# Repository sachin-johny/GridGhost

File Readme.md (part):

<div align="center">
  
  <h2>GridGhost</h2>
  <p><strong>Macro-first PCB auto-placement engine for KiCad</strong></p>
  <p>Treats each IC + its decoupling caps as a single rigid body (a "macro"), places macros net-aware around their I/O attractors, optimizes via simulated annealing, and legalizes — all outside the KiCad editor.</p>
  <br/>
</div>

## Features

- **Macro abstraction** — an IC + its assigned decoupling caps form one `Macro` that moves rigidly through every stage of the pipeline. Caps rotate around the IC, translate with it, and stay within `MAX_CAP_IC_GAP_MM = 4.0` mm **edge-to-edge gap** of the leader — automatically, because the offset is fixed at construction time.
- **Cap classification + assignment** — caps are classified as *decoupling*, *bulk*, or *coupling* before IC assignment. Decoupling caps are distributed round-robin across ICs (one cap → exactly one IC) based on shared power rails and physical proximity.
- **Net-aware initial placement** — clusters components by net connectivity (reusing `engine/net_clustering`), then shelf-packs each cluster around the centroid of the fixed components + placed connectors it shares nets with. Per-macro gap is proportional to macro size (`max(min_gap, max_dim * 0.5)`), giving SA room to move.
- **Connector-attractor pull** — connectors are placed on the perimeter *first*, so interior placement can use their positions as attractors. Interior macros connected to a given connector get pulled toward it (`attractor_pull` blends with grid-cell fallback to prevent pile-up).
- **Simulated annealing** with four move operators:
  - **Translate** — rigid (dx, dy) on one macro
  - **Rotate** — 90/180/270 around the leader; caps orbit
  - **Swap** — exchange leader positions of two macros
  - **Displace-neighbor** — pick a macro, find a macro it overlaps, push the neighbor along the cheaper axis. Helps SA escape jammed configurations.
- **Calibrated T0** — initial temperature is set from overlap-clean sample moves only, so the HPWL gradient SA follows isn't drowned out by the β=25 overlap penalty.
- **Routability-aware cost function** — `α·HPWL + β·Overlap + γ·Boundary + γ·Keepout + rudy·RUDY + pin_density·PinDensity + cap_attraction·CapAttraction + clearance·Clearance`, with **power nets included in HPWL** (the key change vs the legacy pipeline — power-net HPWL is what gives SA gradient signal to keep caps near their assigned IC). RUDY, pin-density, cap-attraction and clearance are default-on so the placer produces a routable result out of the box. See [Cost Function](#cost-function) below.
- **Non-rectangular board outlines** — polygon outlines (connector notches, mouse-bites, castellated edges) and interior holes/keepout zones are honored end-to-end: initial placement, SA's boundary gradient, and the legalizer all clamp to the true outline instead of its outer AABB. Plain rectangular boards trace the exact pre-polygon code paths (zero behavior change).
- **Internal keepout zones** — rectangular no-place zones (mounting holes, board-edge fab notes, etc.) are penalized in the cost function and actively evicted by the legalizer's multi-pass keepout clamp, which pushes an offending macro out along its shallowest exit axis.
- **End-mating connector orientation** — barrel jacks, USB, RJ45, HDMI, D-Sub and other end-mating connectors are oriented so the mating face points outward. Face-mating connectors (terminal blocks, pin headers, SMA) use the perpendicular-to-pad-column heuristic.
- **Iterative legalizer** — grid snap → push-apart → boundary clamp, iterated up to 5 rounds to settle the push-apart ↔ clamp cycle. Cap-IC distance violations are reported as a separate stat. A post-pass **hard-DRC min-gap check** then pushes sub-0.15 mm passive-pair gaps up to the DRC minimum — TestPoint and mechanical-feature pairs are exempt (their tight placement is intentional), and any push that would create a new overlap is rolled back. Alternate strategies (`abacus`, `sa_polish`) are selectable via `--legalizer`.
- **Pad rotation propagation** — footprint rotation rewrites only the footprint's own `(at ...)` expression; per-pad `(at X Y r)` overrides are left untouched, avoiding the double-rotation that previously corrupted asymmetric footprints (SOIC/QFN/offset-pin-1 parts).
- **Edge-connector awareness** — horizontal/surface-mount connectors are placed on the board perimeter and excluded from out-of-bounds counts; vertical/THT connectors are treated as interior components.
- **Net exclusion for SA speed** — `--exclude-nets` drops near-constant-HPWL global nets (board-wide GND/VCC) from SA's per-move cost evaluation, cutting evaluation cost without changing what's optimized.
- **Debug visualization** — `--debug-bbox` draws component bounding boxes and board outline on the `Dwgs.User` layer for visual inspection in KiCad.

## Pipeline (macro-first, `place_v2`)

```text
KiCad .kicad_pcb
       │
  ┌──────────┐   parse S-expressions → BoardModel
  │  parse   │   (components, pads, nets, board outline)
  └────┬─────┘
       │
  ┌──────────┐   1. classify caps (decoupling / bulk / coupling)
  │  build   │   2. assign decoupling caps to ICs (round-robin)
  │ macros   │   3. build Macro per IC leader (+ caps as followers)
  └────┬─────┘   4. connector macros are empty (leader-only)
       │
  ┌──────────┐   place connectors on perimeter FIRST so their
  │connector │   positions can act as attractors for interior
  │ perimeter│   placement
  └────┬─────┘
       │
  ┌──────────┐   cluster interior components by net connectivity,
  │ initial │   shelf-pack each cluster around its attractor point,
  │ interior│   per-macro gap proportional to size
  └────┬─────┘
       │
  ┌──────────┐   simulated annealing on interior macros only
  │   SA     │   (translate / rotate / swap / displace-neighbor)
  │          │   T0 calibrated from overlap-clean sample moves
  └────┬─────┘
       │
  ┌──────────┐   grid snap → push-apart → boundary clamp, iterated
  │ legalize │   + hard-DRC min-gap pass (0.15 mm); reports residual
  │          │   overlaps, boundary failures, and cap-IC violations
  └────┬─────┘
       │
  Updated .kicad_pcb  (+  positions JSON)
```

## CLI Usage

```bash
# Auto-place a board (macro-first pipeline is the default)
python gridghost.py place <input.kicad_pcb> [options]

# Extract board data to JSON (no placement)
python gridghost.py extract <input.kicad_pcb> [-o output.json]

# List available board profiles
python gridghost.py profiles
```

### Place options

| Flag | Default | Description |
|------|---------|-------------|
| `-m`, `--margin` | `5.0` | Board edge margin in mm (`config.json` `placement.margin`) |
| `--grid-mm` | `0.5` | Legalization grid pitch in mm (`config.json` `legalization.grid_mm`) |
| `--sa-iterations` | `max(1500, 25×N)` | SA iterations; scales with macro count when unset (min 1500) |
| `--sa-reheat` | `3` | Number of SA reheat rounds (`config.json` `annealer.reheat_count`) |
| `--alpha` | `1.0` | HPWL weight |
| `--beta` | `25.0` | Overlap penalty weight |
| `--gamma` | `8.0` | Boundary penalty weight (also the default keepout-overlap weight) |
| `--delta` | `0.0` | Constraint-rule penalty weight (decoupling proximity, crystal-MCU, thermal grouping/separation, etc., via `engine/constraint_evaluator.py`). Opt-in — `0` preserves current behavior. |
| `--rudy-weight` | `1.0` | RUDY wire-density congestion penalty (0 = off) |
| `--pin-density-weight` | `0.2` | Pin-escape congestion penalty; complements RUDY (0 = off) |
| `--cap-attraction-weight` | `1.0` | Deadband-linear drift penalty (`max(0, dist − 5mm)`) holding rail-adjacent freed caps near their assigned IC (0 = off) |
| `--clearance-weight` | `5.0` | Pairwise routing-halo clearance charge (`max(0, 1mm − edge_gap)`) between macros; density-tapered (0 = off) |
| `--exclude-nets` | *(none)* | Net names to drop from HPWL during SA (e.g. `--exclude-nets GND +3V3`) — speeds up SA on boards with near-constant, board-wide power nets |
| `--legalizer` | `heuristic` | Overlap-resolution strategy: `heuristic` (grid snap/push-apart/clamp), `abacus` (row-based DP, kept for comparison only), or `sa_polish` (overlap-weighted SA pass) |
| `--seed` | `42` | SA RNG seed (deterministic runs) |
| `--connector-mating-margin` | `5.0` | Edge offset for perimeter connectors |
| `--macro-v2` / `--no-macro-v2` | on | Toggle macro-first pipeline. Default on. `--no-macro-v2` falls back to the legacy grid pipeline (`engine/smart_placement.py`), retained for A/B comparison. |
| `--dry-run` | off | Don't write PCB output file |
| `--debug-bbox` | off | Draw bounding boxes on Dwgs.User layer |
| `-v`, `--verbose` | off | Print per-stage cost breakdown, including routability-term initial/final values even when a term's weight is 0 |

### Examples

```bash
# Auto-place with defaults
python gridghost.py place board.kicad_pcb

# Bigger SA budget for dense boards
python gridghost.py place board.kicad_pcb --sa-iterations 3000 --sa-reheat 4

# Tighter legalization grid
python gridghost.py place board.kicad_pcb --grid-mm 0.5

# Dry run with verbose cost breakdown + debug bboxes
python gridghost.py place board.kicad_pcb -v --dry-run --debug-bbox

# Extract board data without placing
python gridghost.py extract board.kicad_pcb -o board_model.json
```

## Cost Function

```text
Total Cost = α·HPWL + β·Overlap + γ·Boundary + γ·Keepout
             + rudy·RUDY + pin_density·PinDensity
             + cap_attraction·CapAttraction + clearance·Clearance
```

- **HPWL** — Half-perimeter wirelength over all nets. **Power and ground nets are included** — this is the key change vs the legacy pipeline. Caps share power rails with their ICs, so power-net HPWL is the gradient signal that keeps caps near their assigned ICs during SA. `--exclude-nets` can drop specific board-wide nets (e.g. global GND) from this term to speed up SA without changing what it optimizes.
- **Overlap** — Sum of pairwise macro bbox intersection areas. Macros are treated as rigid rectangles (leader + follower union bbox).
- **Boundary** — Distance penalty for components whose bbox extends outside the board outline, computed via the outline's `bbox_overflow()` so it's identical on rectangles and gradient-correct on polygon/notched boards. Edge connectors (intentional overhang) are excluded.
- **Keepout** — Total area of component bboxes intersecting internal keepout zones (mounting holes, fab no-place areas). Weight defaults to `γ` (the boundary weight). Even with this term's SA gradient off, the legalizer's `_keepout_clamp` still actively evicts macros parked inside a keepout, pushing them out along the shallowest exit axis.
- **RUDY** — Wire-density congestion: each net's bounding-box "traffic" spread uniformly across the grid cells it spans, scaled by local component density (0.3× sparse boards, 1.2× dense boards, 1.0× otherwise) so amplification doesn't overshoot already-congested regions. Catches routing choke points HPWL alone is blind to. Default weight `1.0`.
- **Pin density** — Signal-pin count per grid cell (power pins excluded, target adapts to board density). Catches pin-escape congestion — dense clusters of small passives crowding a QFN's pins — that RUDY's wire-density model misses. Default weight `0.2`.
- **Cap attraction** — Deadband-linear drift penalty, `max(0, center_dist − 5mm)`, on *rail-adjacent* freed caps toward their assigned IC. Root-cause fix for shared-rail cap drift: on a rail spanning several ICs the rail's net bbox is already board-wide, so HPWL alone gives a freed cap zero gradient to stay near its IC. Default weight `1.0`.
- **Clearance** — Pairwise routing-halo charge between macro pairs: `max(0, target − edge_gap)`, where the pair's target is the **min of the two members'** per-type targets (default 1.0 mm). Pairs are exempt when both leaders are mechanical features (mounting holes, fiducials, test coupons) or when either member is a TestPoint — probe pads are intentionally pinned to IC pins, and the uniform target charged them for exactly the tight placement the design wants. HPWL's pull and the overlap term's cliff-at-touching otherwise let SA park components at a 0.00 mm gap with no room for a trace; intersecting pairs charge exactly the target so `β` stays the sole "depth" charger. Auto-tapered by interior density (1.0× ≤ 0.45 density, 0.25× ≥ 0.65). Default weight `5.0`.

All four routability terms (Keepout, RUDY, pin density, clearance) plus cap attraction are **default-on**. Pass the matching `--*-weight 0` flag to disable any of them; `-v` always reports each term's initial and final value, even at weight 0.

## Macro Model

A `Macro` is the atomic unit of placement. Construction:

1. **Leader**: a component (typically an IC) that's free to move.
2. **Followers**: caps assigned to that IC. Each follower has a *fixed offset* in leader-local coordinates, chosen at construction time by `find_cap_offset` — an 8-direction fan search at increasing edge-to-edge spacings (0.5–4.0 mm) that:
   - Rejects slots where the cap overlaps the leader or any already-placed sibling.
   - Bounds the cap's **edge-to-edge gap** to the leader by `MAX_CAP_IC_GAP_MM = 4.0` mm (the spacing itself). The gap — not the center-to-center distance — is what governs decoupling effectiveness; center-distance is size-dependent and broke every cap on ICs larger than ~9 mm.
   - Uses `max(cap_w, cap_h)/2` as the cap's half-extent on **both** axes, so the chosen gap survives leader rotation: offsets rotate with the leader but caps don't rotate with it, and a cap-height-based offset would land a non-square cap inside the leader after a 90°/270° rotation.
   - Falls back to the first leader-clear slot (smallest gap) if no slot is sibling-free.

Because offsets are fixed, the cap-IC gap can **never grow at runtime** — translating or rotating the leader applies the same rigid transform to followers. The gap is enforced by construction.

Move operators and the legalizer all operate on macros as opaque rigid bodies. Caps never get separated from their IC.

## Cap Assignment

`assign/assign_caps.py` classifies each capacitor and assigns decoupling caps to ICs. There are four classes:

- **Decoupling (rigid)** (≤ `DECAP_MAX_VALUE_F = 10e-6` F, i.e. ≤ 10 µF) — real decoupling caps whose pins on the IC land in one tight physical cluster (max pairwise pad distance on that net ≤ `RAIL_PAD_SPREAD_THRESHOLD_MM = 3.0` mm). **All** caps the netlist puts on that (IC, rail) pair become rigid `Macro` followers — the count comes from the schematic, not a manual cap — and stay within `MAX_CAP_IC_GAP_MM` edge-to-edge of the leader.
- **Decoupling (rail-adjacent)** — real decoupling caps on a rail whose pins are physically scattered across the IC footprint (e.g. a BGA power net landing on opposite corners). There's no single point to glue a tight rigid ring to, so these become standalone macros; SA holds them near their assigned IC via the **cap→IC attraction** cost term instead of rigid geometry. One IC can have, say, 6 rigid followers on one rail and 2 rail-adjacent on another — the split is per (IC, rail) pair, not a per-IC ceiling.
- **Bulk** (> 10 µF, or on a power rail no IC shares) — stays standalone, not assigned to any IC. Unparseable values default to bulk (conservative).
- **Coupling / signal** — only on signal nets (crystal loads, shields, USB D+/D-, reset filters), no power rail. Standalone.

Decoupling caps are distributed round-robin across the ICs sharing a rail. Power-rail detection also matches hierarchical labels (e.g. `/Buck/VIN`) and KiCad auto-generated net names (e.g. `Net-(U1-VIN)`) via trailing-token power-pin conventions, not just literal `+3V3`/`GND`-style names — deliberately conservative (EN/FB/COMP/SW/BOOT/VG and FET-source pins stay excluded).

A cap assigned to an IC is **only** in that IC's macro — never as a standalone macro. This is critical: if a cap were in two macros, push-apart could move the standalone cap away from its IC. One `assign_caps` classification drives rigid gluing, cap attraction, *and* the legacy `--delta` decoupling-proximity constraint — there's a single source of truth for which caps belong to which IC.

## Project Structure

```text
GridGhost/
├── gridghost.py                   # CLI entry point
├── config.py                      # Typed config loader (dataclasses)
├── config.json                    # Default config (margin, SA, legalization params)
│
├── models/
│   ├── board_model.py             # BoardModel, Component, Net, Pad, BoardOutline
│   │                              # (rectangle or polygon-with-holes; contains/
│   │                              # contains_bbox/fit_bbox_inside/bbox_overflow),
│   │                              # BoardModel.keepouts (rectangular no-place zones)
│   └── macro.py                   # Macro: leader + rigid followers
│                                  # find_cap_offset; MAX_CAP_IC_GAP_MM = 4.0 (edge-to-edge)
│
├── parsers/
│   ├── kicad_parser.py            # S-expression .kicad_pcb parser
│   └── placement_writer.py        # Write placements back to .kicad_pcb / JSON
│
├── assign/
│   └── assign_caps.py             # Classify caps (decoupling / bulk / coupling)
│                                  # and assign decoupling caps to ICs
│
├── cost/
│   ├── cost.py                    # Macro-v2 cost: α·HPWL (incl. power rails) + β·overlap
│   │                              # + γ·boundary + γ·keepout + rudy + pin_density
│   │                              # + cap_attraction + clearance
│   ├── chains.py                  # Signal-flow chain grouping for cost/SA
│   └── incremental.py             # Incremental cost delta for macro SA (all cost terms)
│
├── place/
│   ├── pipeline.py                # 5-stage orchestrator (build → connector →
│   │                              # initial → SA → legalize)
│   ├── initial.py                 # Net-aware clustered shelf-pack with
│   │                              # connector-attractor pull
│   ├── connectors.py              # Perimeter placement with pad-based rotation
│   ├── cluster.py                 # Net clustering + shelf-pack helpers for initial
│   ├── sa.py                      # Macro-aware SA (translate / rotate / swap /
│   │                              # displace-neighbor); calibrated T0
│   ├── sa_polish.py               # Overlap-weighted SA legalizer strategy (--legalizer sa_polish)
│   ├── legalizer.py               # Grid snap → push-apart → boundary clamp,
│   │                              # iterated up to 5 rounds + hard-DRC min-gap
│   │                              # pass (0.15 mm, overlap-rollback safe)
│   └── abacus_bridge.py           # Adapter from rigid Macros to the row-based
│                                  # Abacus legalizer (--legalizer abacus)
│
├── engine/                        # Shared + legacy modules.
│   ├── net_clustering.py          # Hypergraph clustering — reused by place/cluster.py
│   ├── cost_state.py              # Incremental cost state — reused by cost/, place/
│   ├── congestion.py              # Density-adaptive RUDY wire-density + pin-density
│   │                              # congestion maps — reused by cost/, place/sa
│   ├── constraint_evaluator.py    # Constraint penalty evaluation — reused by cost_state
│   ├── group_moves.py             # Macro/group move primitives — reused widely
│   ├── subcircuit_patterns.py     # Subcircuit pattern detection — reused by clustering
│   ├── _pure_graph.py             # Louvain graph core — reused by net_clustering
│   ├── cost_function.py           # Legacy cost function (used by --no-macro-v2 path)
│   ├── moves.py                   # Legacy SA move operators (--no-macro-v2)
│   ├── annealer.py                # Legacy SA engine (--no-macro-v2)
│   ├── placement_prepass.py       # Legacy decap pre-place (--no-macro-v2)
│   ├── grid_placement.py          # Legacy grid / force-directed placement (--no-macro-v2)
│   ├── quadratic_placement.py     # Legacy quadratic placer (--no-macro-v2)
│   └── smart_placement.py         # Legacy grid pipeline (--no-macro-v2)
│
├── legalization/
│   ├── legalizer.py               # Component-level legalizer (grid snap / push-apart /
│   │                              # boundary clamp), used by both pipelines
│   ├── abacus_legalizer.py        # Row-based Abacus DP legalizer
│   ├── post_legalize.py           # Post-legalization HPWL recovery (cell slide / pair swap)
│   └── spatial_grid.py            # Spatial hash grid for overlap acceleration
│
├── profiles/
│   └── board_profiles.py          # Cost weights + constraint rules per board type
│
├── utils/
│   ├── courtyard.py               # Courtyard/bbox helpers for the parser
│   ├── density.py                 # Pack-density target + board-area checks
│   └── display.py                 # CLI formatting (summary, cost, component table)
│
├── samples/
│   └── sample_board.py            # 18-component MCU peripheral sample board
│
├── tests/
│   ├── test_macro.py              # Macro model: rigid moves, bounds, cap gap, bbox
│   ├── test_assign_caps.py        # Cap classification + IC assignment (rigid/rail-adjacent split)
│   ├── test_cost.py               # HPWL / overlap / boundary / keepout / cap-attraction / clearance cost
│   ├── test_incremental_cost.py   # Incremental cost delta (all terms)
│   ├── test_chains.py             # Signal-flow chain grouping
│   ├── test_connector_placement.py# Perimeter connector placement + rotation
│   ├── test_placement_spread.py   # Placement spread / coverage
│   ├── test_abacus_bridge.py      # Macro → Abacus legalizer adapter
│   ├── test_sa_polish.py          # SA-polish legalizer strategy
│   ├── test_nonrect_outline.py    # Polygon outline geometry, parser tracing, legalizer clamps
│   ├── test_keepout.py            # Internal keepout cost + legalizer eviction
│   ├── test_pad_rotation.py       # Footprint-only rotation (no double-rotation on pads)
│   ├── test_overlap_regression.py # (currently disabled — 0 collected)
│   ├── test_phase1.py             # 87 tests: legacy pipeline + data model
│   ├── run_all.py / dashboard.py / visualizer.py   # Batch run + result dashboard harness
│   ├── run_benchmark.py           # Benchmark harness for placement quality/timing
│   ├── README.md                  # Test harness usage (run_all, dashboard, visualizer)
│   ├── test_pcbs/                 # Bundled .kicad_pcb boards + reference JSONs
│   └── external_boards/rl_pcb/    # Third-party reference boards (see its own README/LICENSE)
│
├── patches/                       # (untracked) benchmark scripts + result JSONs
│
├── logo.png
├── CLAUDE.md                      # AI assistant context
└── README.md                      # This file
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
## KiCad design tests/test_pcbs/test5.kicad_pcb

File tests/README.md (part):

# Tests & Benchmarking

Test suites, measurement harnesses, benchmark boards, and a unified
orchestrator that runs everything and produces an HTML dashboard with
per-board visualizations.

## Quick start — the unified harness

The fastest way to run everything is the **unified orchestrator**:

```bash
python tests/run_all.py                       # run all phases
python tests/run_all.py --skip-external       # skip the slow external-boards phase
python tests/run_all.py --only cbb test4      # only specific boards
python tests/run_all.py --rudy-weight 0.3     # enable RUDY in SA
python tests/run_all.py --skip-unit-tests --skip-overlap-regression  # just placement + viz
```

It runs five phases in order, collects all results, and writes a
self-contained HTML dashboard to `tests/output/<run_id>/`:

1. **Unit tests** — `python -m pytest tests/` (falls back to standalone
   `main()` if pytest is missing). Fast correctness gate (~80s).
2. **Placement pipeline** — runs `place_v2` in-process on every board
   in `tests/test_pcbs/`. Captures HPWL, overlaps, density, RUDY,
   cap-IC distances, component-type breakdown, and per-phase timing.
3. **CLI smoke test** — runs `python gridghost.py place` end-to-end on
   each board via subprocess. Catches CLI-only bugs the in-process
   path misses.
4. **Overlap regression** — runs `tests/test_overlap_regression.py`
   (self-report vs independent scan). The standing check from the
   evaluation fix.
5. **External boards** — same as Phase 2 but on
   `tests/external_boards/rl_pcb/*.kicad_pcb` (9 real-world boards).
   Adds ~10 min but catches real-world edge cases.

**Outputs** (under `tests/output/<run_id>/`):
- `dashboard.html` — the main deliverable. Open in any browser.
- `results.json` — raw metrics (for programmatic comparison).
- `<board>.svg` — per-board SVG (also inlined in the dashboard).
- `<board>_placed.kicad_pcb` — placed output (open in KiCad).
- `unit_tests.log`, `cli_smoke_<board>.log` — raw phase logs.

### Dashboard contents

The dashboard is a single self-contained HTML file (no external CSS/JS)
with:

- **Header** — run ID, timestamp, git commit, summary cards (boards,
  passing, total overlaps, total wall-time).
- **Phase summaries** — one card per phase with pass/fail status,
  passed/failed counts, duration.
- **KPI table** — one row per board, columns for components, ICs, caps,
  overlaps, Edge.Cuts present, density, HPWL, RUDY peak, SA time,
  legalize time, total time.
- **Aggregate charts** — overlaps per board (bar), timing breakdown
  (stacked bar), component-type distribution (stacked bar), cap → IC
  distance histogram.
- **Per-board detail** — inline SVG visualization + metric chips +
  overlap-pair list (collapsible) + cap-IC distance stats.

### Visualization features

The SVG visualization (rendered by `tests/visualizer.py`) shows:

- Board outline (Edge.Cuts) as a solid black rectangle.
- Margin ring (light grey fill between outline and interior bbox).
- Interior bbox (dashed green) — the region SA + legalizer clamp to.
- All components colored by type (ICs red, caps blue, resistors green,
  connectors orange, mounting holes grey cross, generic light grey).
- Overlap pairs highlighted with a red fill + red border.
- Decoupling cap → IC leader lines (thin grey dashed).
- Connector pad dots (small black circles) so overhang is visible.
- Mounting hole cross marks.
- Per-component labels for ICs and large components (ref + size).
- Legend in the top-right corner.
- Overlap count badge in the top-left.

### What to look for in the dashboard

When reviewing a run, scan top-to-bottom:

1. **Header summary cards** — if "Total overlaps" is non-zero or
   "Passing" is less than total boards, drill into the KPI table.
2. **Phase cards** — every phase should be PASS. FAIL in unit tests
   means a regression in core functionality. FAIL in placement_test_pcbs
   means at least one board has overlaps. FAIL in CLI smoke means the
   CLI itself is broken (arg parsing, file write, hash-seed re-exec).
   FAIL in overlap_regression means the legalizer's self-report
   disagrees with an independent scan — the original symptom of
   Findings 1 & 2.
3. **KPI table** — sort by "Overlaps" column. Red rows have overlaps;
   green rows are clean. "Edge.Cuts" should be ✓ for every board
   (Finding 1 fix). "Density" should sit between 0.20 and 0.55
   (matching `target_pack_density`).
4. **Aggregate charts**:
   - *Overlaps per board* — any red bar is a board to investigate.
   - *Timing breakdown* — SA dominates (orange). If parse (cyan) is
     >10% of total, the parser may have a regression.
   - *Component-type distribution* — sanity check the parser. A board
     with 0 caps but 5 ICs suggests cap detection is broken.
   - *Cap → IC distance* — most caps should be in the 0-8mm buckets
     (green). Caps in the 12+ bucket (red) violate the decoupling
     proximity rule.
5. **Per-board sections** — open the SVG. Overlapping components are
   outlined in red with a light red fill. Decoupling caps are connected
   to their IC by a thin grey dashed line. Connector pad dots show
   where copper lands. The "⚠ N overlaps" badge in the top-left gives
   the quick verdict.

### Timing expectations

Typical wall-clock per phase on a modern laptop:

| Phase | Test boards (6) | + External boards (9) |
|-------|----------------:|----------------------:|
| Unit tests | ~80-100s | — |
| Placement pipeline | ~30-60s | +5-10 min |
| CLI smoke test | ~30-60s | (skipped by default for external) |
| Overlap regression | ~60-90s | — |
| Dashboard generation | <2s | — |
| **Total** | **~3-5 min** | **~10-15 min** |

For daily use, `--skip-external` brings it to ~5 min. For quick
iteration on a single board, `--only cbb --skip-unit-tests
--skip-overlap-regression --skip-cli-smoke` runs in ~25s.

### Troubleshooting

**"Phase: Placement Test Pcbs — FAIL" with `overlaps=-1`**
The placement pipeline raised an exception. Check the per-board
"error" field in `results.json`. Common causes: malformed `.kicad_pcb`
input, OOM on very large boards, or a regression in `place_v2`.

**"Phase: Cli Smoke — FAIL"**
The CLI itself is broken. Open `cli_smoke_<board>.log` to see stdout.
Common causes: missing dependency (numpy), PYTHONHASHSEED re-exec loop,
or an arg-parsing regression in `gridghost.py`.

**"Phase: Overlap Regression — FAIL"**
The legalizer's self-reported overlap count disagrees with an
independent re-parse-and-scan of the output file. This is the standing
check from the placement-evaluation fix — see `test_overlap_regression.py`'s
docstring. Open `overlap_regression.log` to see which board(s) failed.

**SVG renders but is empty / missing components**
Check that the board's `*_placed.kicad_pcb` was actually written. If
`apply_placement` failed mid-write, the model may have positions but
the file may be missing components. Re-run with `--only <board>` to
isolate.

**Dashboard opens but charts are squished / unreadable**
The dashboard uses CSS grid with `minmax(380px, 1fr)` for charts. If
your browser window is narrower than 760px, charts stack vertically
and may look cramped. Widen the window or zoom out.

### Standalone SVG visualization

The visualizer can be run on any placed `.kicad_pcb` without going
through the full harness:

```bash
# Render a placed board to SVG
python tests/visualizer.py tests/output/run_xxx/cbb_placed.kicad_pcb --out cbb.svg

# Larger SVG, no labels (for thumbnails)
python tests/visualizer.py cbb_placed.kicad_pcb --out cbb.svg --width 1200 --no-labels

# Hide decap leader lines and pad dots (cleaner look for slides)
python tests/visualizer.py cbb_placed.kicad_pcb --out cbb.svg --no-decaps --no-pads
```

Flags: `--width` (pixels, default 800), `--title`, `--no-labels`,
`--no-pads`, `--no-decaps`.

### Programmatic access to results

Each run writes `results.json` alongside `dashboard.html`. Structure:

```json
{
  "run_id": "run_20250726_120000",
  "timestamp": "20250726_120000",
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
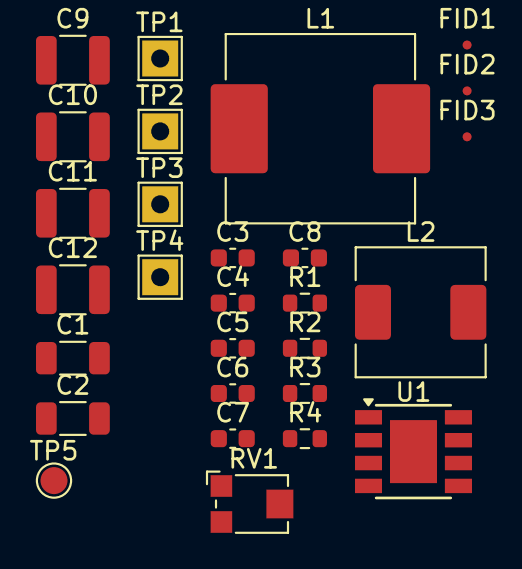
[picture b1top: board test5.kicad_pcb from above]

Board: 2 copper layers, 28 parts (0 on the bottom side), 12 nets, no tracks yet.

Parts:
C1, C2: 10µF; C_1206_3216Metric
C3, C4, C8: 100nF; C_0603_1608Metric
C5, C7: 10nF; C_0603_1608Metric
C6: 2.7nF; C_0603_1608Metric
C9, C10, C11, C12: 22µF; C_1210_3225Metric
FID1, FID2, FID3: Fiducial; Fiducial_0.5mm_Mask1mm
L1: 3.6µH; L_Vishay_IHLP-4040
L2: 10µH; L_Wuerth_HCM-7050
R1: 100kΩ; R_0603_1608Metric
R2: 15.8kΩ; R_0603_1608Metric
R3: 2.2kΩ; R_0603_1608Metric
R4: 100Ω; R_0603_1608Metric
RV1: 47kΩ; Potentiometer_Bourns_TC33X_Vertical
TP1, TP2, TP3, TP4: TestPoint; TestPoint_THTPad_2.0x2.0mm_Drill1.0mm
TP5: TestPoint; TestPoint_Pad_D1.5mm
U1: AP64501SP-13; Diodes_SO-8EP

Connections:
GND: C1.2, C2.2, C3.2, C5.2, C6.2, C8.2, C9.2, C10.2, C11.2, C12.2, R3.2, TP2.1 (1_1), TP4.1 (1_1), U1.7 (GND), U1.9 (EP)
unnamed: C6.1, R2.2
unnamed: C7.2, C8.1, C9.1, C10.1, C11.1, L1.2, L2.1, RV1.1
unnamed: C12.1, L2.2, TP3.1 (1_1)
unnamed: R4.2, RV1.2, RV1.3
unnamed: C4.1, U1.1 (BST)
unnamed: R2.1, U1.6 (COMP)
unnamed: R1.2, TP5.1 (1_1), U1.3 (EN)
unnamed: C7.1, R3.1, R4.1, U1.5 (FB)
unnamed: C5.1, U1.4 (SS)
unnamed: C4.2, L1.1, U1.8 (SW)
unnamed: C1.1, C2.1, C3.1, R1.1, TP1.1 (1_1), U1.2 (VIN)

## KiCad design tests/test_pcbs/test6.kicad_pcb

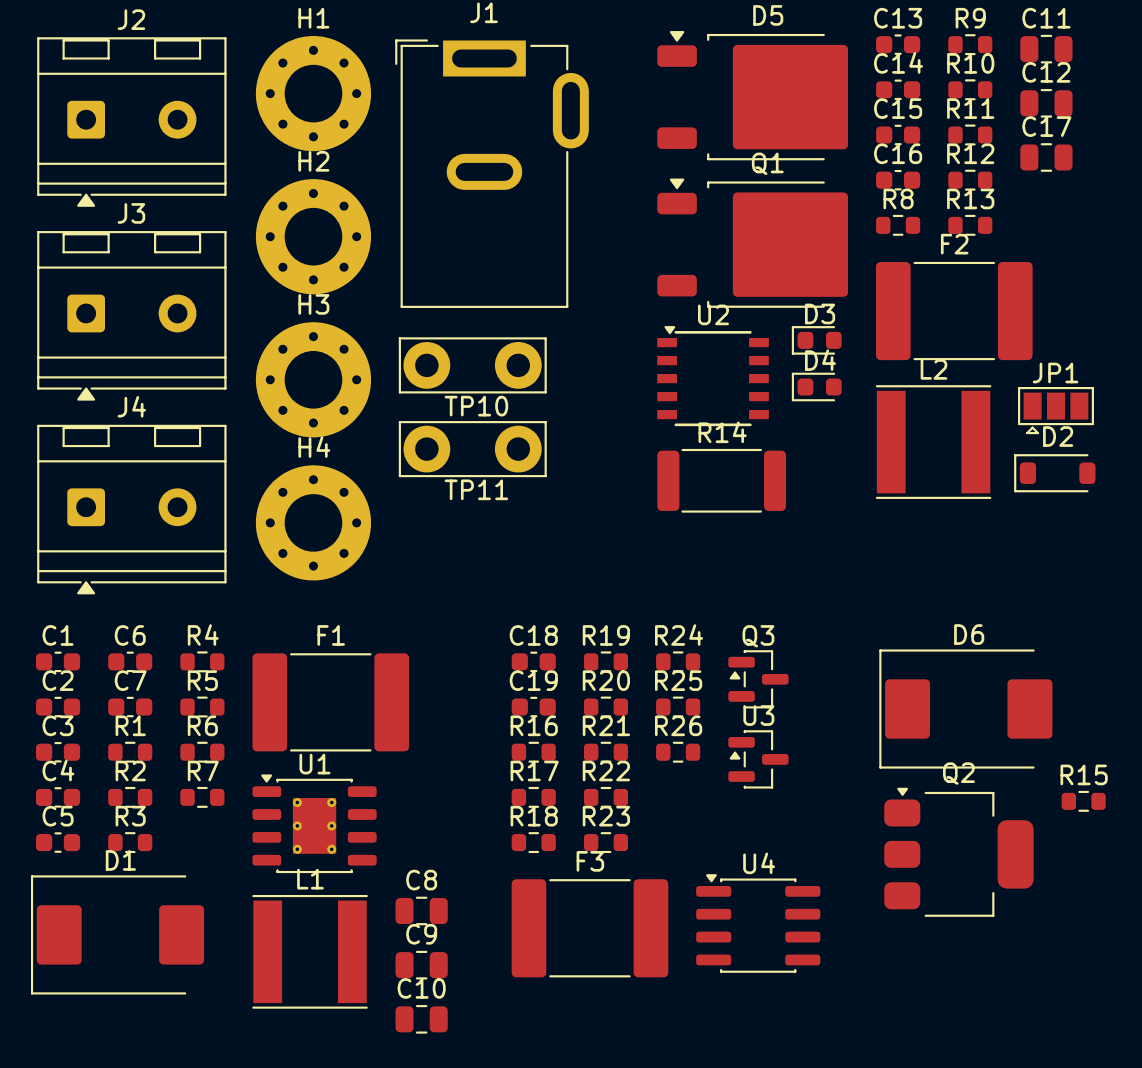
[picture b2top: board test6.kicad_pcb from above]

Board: 2 copper layers, 74 parts (0 on the bottom side), 39 nets, no tracks yet.

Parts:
C1, C2, C3, C4: 2u2; C_0603_1608Metric
C5, C13, C14, C16, C18: 100n; C_0603_1608Metric
C6: 4n7; C_0603_1608Metric
C7: 47p; C_0603_1608Metric
C8, C9, C10, C11, C12, C17: 47u; C_0805_2012Metric
C15: 220n; C_0603_1608Metric
C19: 10n; C_0603_1608Metric
D1, D6: SS54; D_SMC
D2: 5V1; D_SOD-123
D3, D4: LED; LED_0603_1608Metric
D5: MBRD20100CT; TO-252-2
F1, F2, F3: 500/24N; Fuse_2920_7451Metric
H1, H2, H3, H4: MountingHole_Pad; MountingHole_3.2mm_M3_Pad_Via
J1: Barrel_Jack_Switch; BarrelJack_GCT_DCJ200-10-A_Horizontal
J2, J3, J4: Screw_Terminal_01x02; TerminalBlock_RND_205-00232_1x02_P5.08mm_Horizontal
JP1: MPPT; SolderJumper-3_P1.3mm_Open_Pad1.0x1.5mm
L1, L2: 10u; L_Taiyo-Yuden_NR-60xx
Q1: DMP4051LK3-13; TO-252-2
Q2: NTF6P02; SOT-223-3_TabPin2
Q3: 2N7002; SOT-23
R1: 442k; R_0603_1608Metric
R2: 90k9; R_0603_1608Metric
R3: 243k; R_0603_1608Metric
R4: 16k9; R_0603_1608Metric
R5: 49R9; R_0603_1608Metric
R6: 33k; R_0603_1608Metric
R7: 2k2; R_0603_1608Metric
R8, R11, R15: 100k; R_0603_1608Metric
R9: 1M; R_0603_1608Metric
R10: 360k; R_0603_1608Metric
R12, R16, R22, R23, R24, R26: 10k; R_0603_1608Metric
R13: 120R; R_0603_1608Metric
R14: 0R12; R_2512_6332Metric
R17, R18, R19: 47k; R_0603_1608Metric
R20: 15k; R_0603_1608Metric
R21: 4k7; R_0603_1608Metric
R25: 10R; R_0603_1608Metric
TP10, TP11: TestPoint_Alt; TestPoint_Bridge_Pitch5.08mm_Drill1.3mm
U1: TPS54360DDA; HSOP-8-1EP_3.9x4.9mm_P1.27mm_EP2.41x3.1mm_ThermalVias
U2: CN3767; SSOP-10_3.9x4.9mm_P1.00mm
U3: TL431AIDBZR; SOT-23
U4: LM393; SOIC-8_3.9x4.9mm_P1.27mm

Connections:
+12V: C8.2, C9.2, C10.2, D6.2 (A), L1.2, Q2.1 (G), R5.1, R15.2
/Battery Protect/BAT+: F3.1, J3.1, TP10.1 (1_1)
/Battery Protect/P+: C16.1, C17.1, C18.1, Q2.2 (D), R14.2, R16.1, R17.1, R20.1, R22.1, U2.7 (BAT), U4.8 (V+)
/Buck/VIN: F1.1, F2.1, J1.1, J2.1
/ByPass/OUTBP: D6.1 (K), J4.1, Q2.3 (S)
GND: C1.1, C2.1, C3.1, C4.1, C6.2, C7.2, C8.1, C9.1, C10.1, C11.2, C12.2, C13.2, C15.2, C16.2, C17.2, C18.2, D1.2 (A), D2.2 (A), D5.3 (A), H1.1 (1_1), H2.1 (1_1), H3.1 (1_1), H4.1 (1_1), J1.2, J2.2, J3.2, J4.2, Q3.2 (S), R2.2, R3.2, R7.2, R11.2, R15.1, R19.2, R21.2, R24.2, TP11.1 (1_1), U1.7 (GND), U1.9 (GNDPAD), U2.2 (GND), U3.3 (A), U4.4 (V-)
unnamed: C6.1, R4.2
unnamed: C15.1, R13.2
unnamed: C19.2, R26.2
unnamed: C5.2, D1.1 (K), L1.1, U1.8 (SW)
unnamed: D2.1 (K), JP1.3 (B), R8.2
unnamed: D3.2 (A), D4.2 (A), R12.2
unnamed: D3.1 (K), U2.4 (DONE)
unnamed: D4.1 (K), U2.3 (CHRG)
unnamed: D5.2 (K), L2.1
unnamed: JP1.1 (A), R10.2, R11.1
unnamed: JP1.2 (C), U2.6 (MPPT)
unnamed: D5.1 (A), Q1.2 (D)
unnamed: Q1.1 (G), U2.10 (DRV)
unnamed: C11.1, C12.1, C13.1, C14.1, F2.2, Q1.3 (S), R8.1, R9.1, R12.1, U2.9 (VCC)
unnamed: Q3.3 (D), R25.2
unnamed: Q3.1 (G), R23.2, R24.1
unnamed: C19.1, R25.1, R26.1
unnamed: R5.2, R6.1
unnamed: R9.2, R10.1
unnamed: R22.2, R23.1, U4.1
unnamed: C5.1, U1.1 (BOOT)
unnamed: C7.1, R4.1, U1.6 (COMP)
unnamed: R1.2, R2.1, U1.3 (EN)
unnamed: R6.2, R7.1, U1.5 (FB)
unnamed: R3.1, U1.4 (RT/CLK)
unnamed: C1.2, C2.2, C3.2, C4.2, F1.2, R1.1, U1.2 (VIN)
unnamed: R13.1, U2.5 (COM)
unnamed: L2.2, R14.1, U2.8 (CSP)
unnamed: C14.2, U2.1 (VG)
unnamed: R16.2, U3.1 (K), U3.2 (REF), U4.2 (-)
unnamed: R20.2, R21.1, U4.3 (+)
unnamed: R17.2, R18.1, U4.5 (+)
unnamed: R18.2, R19.1, U4.6 (-)

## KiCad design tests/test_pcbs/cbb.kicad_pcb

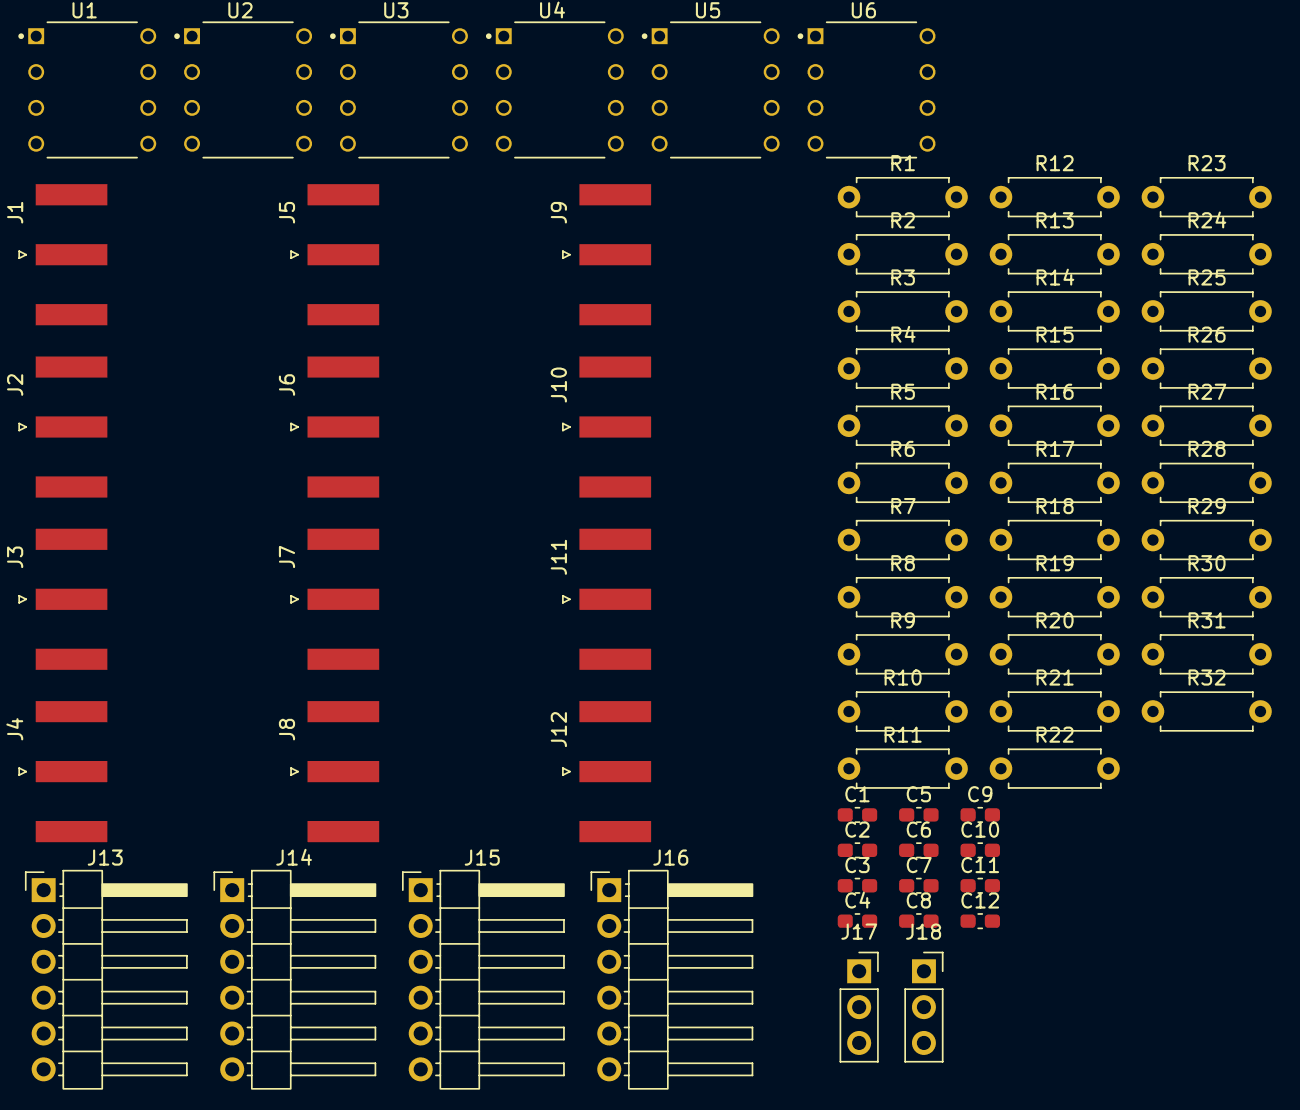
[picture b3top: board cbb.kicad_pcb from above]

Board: 2 copper layers, 68 parts (0 on the bottom side), 42 nets, no tracks yet.

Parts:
C1, C2, C3, C4, C5, C6, C7, C8, C9, C10, C11, C12: 100nF; C_0603_1608Metric_Pad1.08x0.95mm_HandSolder
J1: +3V3 LM6482; SMA_Amphenol_132289_EdgeMount
J2: -3V3 LM6482; SMA_Amphenol_132289_EdgeMount
J3: -12V OPA2227P; SMA_Amphenol_132289_EdgeMount
J4: +12V OPA2227P; SMA_Amphenol_132289_EdgeMount
J5: ADC1_in; SMA_Amphenol_132289_EdgeMount
J6: ADC2_in; SMA_Amphenol_132289_EdgeMount
J7: ADC3_in; SMA_Amphenol_132289_EdgeMount
J8: ADC4_in; SMA_Amphenol_132289_EdgeMount
J9: Buffer1_out; SMA_Amphenol_132289_EdgeMount
J10: Buffer2_out; SMA_Amphenol_132289_EdgeMount
J11: Buffer3_out; SMA_Amphenol_132289_EdgeMount
J12: Buffer4_out; SMA_Amphenol_132289_EdgeMount
J13: ADC_out_1-2; PinHeader_1x06_P2.54mm_Horizontal
J14: ADC_out_3-4; PinHeader_1x06_P2.54mm_Horizontal
J15: DAC_in_1-2; PinHeader_1x06_P2.54mm_Horizontal
J16: DAC_in_3-4; PinHeader_1x06_P2.54mm_Horizontal
J17: 12V power share; PinSocket_1x03_P2.54mm_Vertical
J18: 3V3 power share; PinSocket_1x03_P2.54mm_Vertical
R1, R2, R3, R4, R5, R6, R7, R8, R9, R10, R11, R12, R13, R14, R15, R16, R17, R18, R19, R20, R21, R22, R23, R24, R25, R26, R27, R28: 22k; R_Axial_DIN0207_L6.3mm_D2.5mm_P7.62mm_Horizontal
R29, R30, R31, R32: 47; R_Axial_DIN0207_L6.3mm_D2.5mm_P7.62mm_Horizontal
U1: ADC-DAC1 LMC6482IN; DIP794W45P254L959H508Q8
U2: ADC-DAC2 LMC6482IN; DIP794W45P254L959H508Q8
U3: ADC-DAC3 LMC6482IN; DIP794W45P254L959H508Q8
U4: BUF2 OPA2227P; DIP794W45P254L959H508Q8
U5: BUF1 OPA2227P; DIP794W45P254L959H508Q8
U6: ADC-DAC4 LMC6482IN; DIP794W45P254L959H508Q8

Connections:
+3V3: C4.2, C5.2, C7.2, C11.2, J1.1 (In), J18.1, R1.1, R3.1, R5.1, R7.1, R9.1, R11.1, R24.1, R26.1, U1.8 (V+), U2.8 (V+), U3.8 (V+), U6.8 (V+)
+12V: C1.1, C9.1, J4.1 (In), J17.1, U4.8 (V+), U5.8 (V+)
-3V3: C3.1, C6.1, C8.1, C12.1, J2.1 (In), J18.3, U1.4 (V-), U2.4 (V-), U3.4 (V-), U6.4 (V-)
-12V: C2.1, C10.1, J3.1 (In), J17.3, U4.4 (V-), U5.4 (V-)
/3.3V: J13.1, J14.1, J15.1, J16.1
/ADC1_in: J5.1 (In), R2.1
/ADC1_out: J13.6, U1.1 (OUTA), U1.2 (NEGA)
/ADC2_in: J6.1 (In), R6.1
/ADC2_out: J13.4, U2.1 (OUTA), U2.2 (NEGA)
/ADC3_in: J7.1 (In), R10.1
/ADC3_out: J14.6, U3.1 (OUTA), U3.2 (NEGA)
/ADC4_in: J8.1 (In), R25.1
/ADC4_out: J14.4, U6.1 (OUTA), U6.2 (NEGA)
/Buffer1_out: J9.1 (In), R29.2
/Buffer2_out: J10.1 (In), R30.2
/Buffer3_out: J11.1 (In), R31.2
/Buffer4_out: J12.1 (In), R32.2
/DAC1_in: J15.6, U1.5 (POSB)
/DAC2_in: J15.4, U2.5 (POSB)
/DAC3_in: J16.6, U3.5 (POSB)
/DAC4_in: J16.4, U6.5 (POSB)
GND: C1.2, C2.2, C3.2, C4.1, C5.1, C6.2, C7.1, C8.2, C9.2, C10.2, C11.1, C12.2, J1.2 (Ext), J2.2 (Ext), J3.2 (Ext), J4.2 (Ext), J5.2 (Ext), J6.2 (Ext), J7.2 (Ext), J8.2 (Ext), J9.2 (Ext), J10.2 (Ext), J11.2 (Ext), J12.2 (Ext), J13.2, J13.3, J13.5, J14.2, J14.3, J14.5, J15.2, J16.2, J17.2, J18.2, R12.1, R13.1, R15.2, R17.2, R18.2, R19.1, R22.1, R28.2
unnamed: R3.2, R4.2, U1.6 (NEGB)
unnamed: R4.1, R17.1, U1.7 (OUTB), U5.3 (+IN_A)
unnamed: R1.2, R2.2, U1.3 (POSA)
unnamed: R7.2, R8.2, U2.6 (NEGB)
unnamed: R8.1, R18.1, U2.7 (OUTB), U5.5 (+IN_B)
unnamed: R5.2, R6.2, U2.3 (POSA)
unnamed: R11.2, R14.2, U3.6 (NEGB)
unnamed: R14.1, R15.1, U3.7 (OUTB), U4.3 (+IN_A)
unnamed: R9.2, R10.2, U3.3 (POSA)
unnamed: R27.1, R28.1, U4.5 (+IN_B), U6.7 (OUTB)
unnamed: R12.2, R16.1, U4.2 (-IN_A)
unnamed: R13.2, R23.1, U4.6 (-IN_B)
unnamed: R16.2, R31.1, U4.1 (OUT_A)
unnamed: R23.2, R32.1, U4.7 (OUT_B)
unnamed: R19.2, R20.1, U5.2 (-IN_A)
unnamed: R21.1, R22.2, U5.6 (-IN_B)
unnamed: R20.2, R29.1, U5.1 (OUT_A)
unnamed: R21.2, R30.1, U5.7 (OUT_B)
unnamed: R26.2, R27.2, U6.6 (NEGB)
unnamed: R24.2, R25.2, U6.3 (POSA)

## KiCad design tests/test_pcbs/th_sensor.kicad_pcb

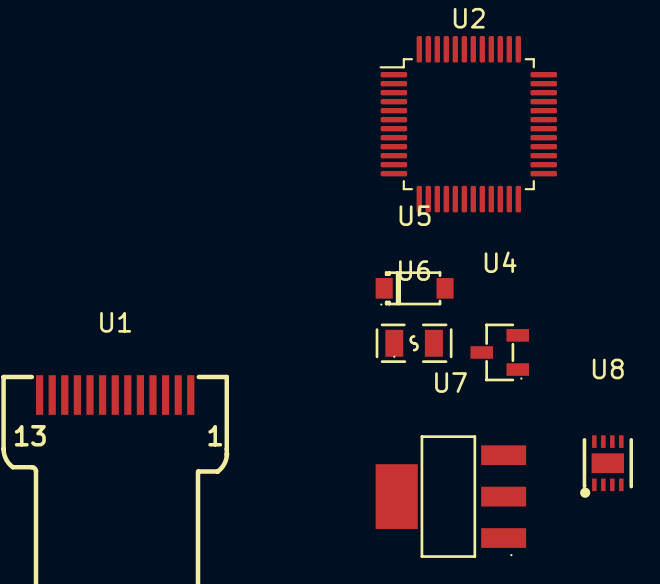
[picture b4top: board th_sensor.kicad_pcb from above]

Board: 2 copper layers, 7 parts (0 on the bottom side), 10 nets, no tracks yet.

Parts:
U1: N096-1608TBBIG11-H13; OLED-SMD_ST7735S
U2: STM32F103C8T6; LQFP-48_7x7mm_P0.5mm
U4: AO3401CI-ES; SOT-23-3_L2.9-W1.3-P1.90-LS2.4-BR
U5: PTVS5V0S1UR,115; SOD-123_L2.8-W1.8-LS3.7-RD
U6: SMD0805-050-24; F0805
U7: MIC5239-3.3YS-TR; SOT-223-3_L6.5-W3.4-P2.30-LS7.0-BR
U8: SHT30-DIS-B2.5KS; DFN-8_L2.5-W2.5-P0.50-BL-EP

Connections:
/DISP_DC: U1.5 (RS), U2.10 (PA0)
/I2C0_SCL: U2.42 (PB6), U8.4 (SCL)
/I2C0_SDA: U2.43 (PB7), U8.1 (SDA)
/PWR_INPUT/VBUS_FUSE: U4.2 (S), U6.2
/PWR_INPUT/VBUS_RAW: U5.1 (C), U6.1
/SPI0_CS_DISP: U1.7 (CS), U2.14 (PA4)
/VBUS_5V: U4.3 (D), U7.1 (IN)
/V_3V3: U1.10 (VDD), U2.1 (VBAT), U2.9 (VDDA), U2.24 (VDD), U2.36 (VDD), U2.48 (VDD), U8.6 (nRESET)
GND: U1.8 (GND), U1.13 (GND), U2.8 (VSSA), U2.23 (VSS), U2.35 (VSS), U2.47 (VSS), U5.2 (A), U7.2 (GND), U8.8 (VSS)
unnamed: U8.2 (ADDR), U8.9 (EPAD)

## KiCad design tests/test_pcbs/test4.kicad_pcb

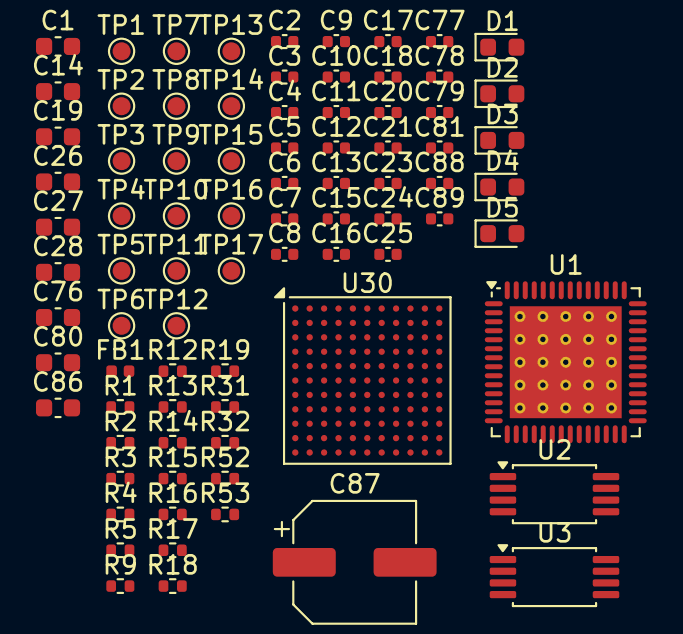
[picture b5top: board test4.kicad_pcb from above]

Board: 2 copper layers, 82 parts (0 on the bottom side), 53 nets, no tracks yet.

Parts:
C1, C14, C19, C26, C27, C28, C76, C80, C86: 4u7; C_0603_1608Metric
C2, C3, C4, C5, C6, C7, C8, C9, C10, C13, C15, C16, C17, C18, C20, C21, C23, C24, C25, C77, C78, C79, C81, C88, C89: u1; C_0402_1005Metric
C11, C12: 9p; C_0402_1005Metric
C87: 150u; CP_Elec_6.3x5.9
D1: GRN; LED_0603_1608Metric
D2: WHT; LED_0603_1608Metric
D3: BLU; LED_0603_1608Metric
D4: ORA; LED_0603_1608Metric
D5: RED; LED_0603_1608Metric
FB1: 600R, 0.5A; L_0402_1005Metric
R1, R2, R13, R14: 2k2; R_0402_1005Metric
R3, R4, R5, R9, R17: 100k; R_0402_1005Metric
R12, R18, R19: 10k; R_0402_1005Metric
R15, R16: 1k; R_0402_1005Metric
R31, R32: 100R; R_0402_1005Metric
R52, R53: 5k1; R_0402_1005Metric
TP1, TP8: 5V; TestPoint_Pad_D1.0mm
TP2, TP17: 1V2; TestPoint_Pad_D1.0mm
TP3, TP7, TP9: 3V3; TestPoint_Pad_D1.0mm
TP4, TP10: SDA; TestPoint_Pad_D1.0mm
TP5, TP11: SCL; TestPoint_Pad_D1.0mm
TP6: CLKREF; TestPoint_Pad_D1.0mm
TP12: GND; TestPoint_Pad_D1.0mm
TP13: VBUS; TestPoint_Pad_D1.0mm
TP14: USBGND; TestPoint_Pad_D1.0mm
TP15: USBDP; TestPoint_Pad_D1.0mm
TP16: USBDM; TestPoint_Pad_D1.0mm
U1: CY7C68013A-56LTX; Cypress_QFN-56-1EP_8x8mm_P0.5mm_EP6.22x6.22mm_ThermalVias
U2: CAT24M01X; TSSOP-8_4.4x3mm_P0.65mm
U3: BL24C256A-SFRC; TSSOP-8_4.4x3mm_P0.65mm
U30: ICE40HX8K-BG121; BGA-121_9.0x9.0mm_Layout11x11_P0.8mm_Ball0.4mm_Pad0.35mm_NS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

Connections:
+1V2: C14.1, C18.1, C24.1, C25.1, C27.1, C77.1, R31.2, R32.2, TP2.1 (1_1), TP17.1 (1_1), U30.D4 (VCC), U30.D8 (VCC), U30.H4 (VCC), U30.H8 (VCC)
+3V3: C1.1, C2.1, C3.1, C4.1, C5.1, C6.1, C7.1, C9.1, C10.1, C15.1, C17.1, C19.1, C20.1, C21.1, C23.1, C28.1, C81.1, R1.2, R2.2, R4.1, R12.1, R17.2, TP3.1 (1_1), TP9.1 (1_1), U1.3 (AVCC), U1.7 (AVCC), U1.11 (VCC), U1.17 (VCC), U1.27 (VCC), U1.32 (VCC), U1.43 (VCC), U1.44 (WAKEUP), U1.55 (VCC), U2.2 (A1), U2.8 (VCC), U3.1 (A0), U3.8 (VCC), U30.C10 (VPP_2V5), U30.H6 (VCCIO_2), U30.L11 (VCC_SPI)
+5V: C16.1, C26.2, C86.2, C87.1, TP1.1 (1_1), TP8.1 (1_1)
/A0: U1.37 (PA4/FIOADDR0), U30.K3 (IOB_63)
/A1: U1.38 (PA5/FIOADDR1), U30.L2 (IOB_61)
/CLKIF: TP7.1 (1_1), U1.13 (IFCLK), U30.K6 (IOB_82_GBIN4)
/CLKREF: TP6.1 (1_1), U1.54 (CLKOUT), U30.L5 (IOB_81_GBIN5)
/D0: U1.18 (PB0/FD0), U30.H7 (IOB_87)
/D1: U1.19 (PB1/FD1), U30.J7 (IOB_86)
/D2: U1.20 (PB2/FD2), U30.J9 (IOB_106_SDI)
/D3: U1.21 (PB3/FD3), U30.K10 (IOB_108_SS)
/D4: U1.22 (PB4/FD4), U30.L10 (IOB_107_SCK)
/D5: U1.23 (PB5/FD5), U30.K9 (IOB_105_SDO)
/D6: U1.24 (PB6/FD6), U30.L8 (IOB_103_CBSEL0)
/D7: U1.25 (PB7/FD7), U30.K7 (IOB_89)
/ENVA: R18.1, U1.45 (PD0/FD8)
/ENVB: R19.1, U1.51 (PD6/FD14)
/FLAGA: U1.29 (CTL0/FLAGA), U30.L7 (IOB_94)
/FLAGB: U1.30 (CTL1/FLAGB), U30.K5 (IOB_79)
/FLAGC: U1.31 (CTL2/FLAGC), U30.L4 (IOB_72)
/FLAGD: U1.40 (PA7/FLAGD/~SLCS), U30.J3 (IOB_57)
/FPGA_DONE: U1.36 (PA3/WU2), U30.K8 (CDONE)
/GNDPLL0: C76.2, C78.2, U30.L6 (GNDPLL0)
/GNDPLL1: C79.2, C80.2, U30.C5 (GNDPLL1)
/LED_ACT: R15.1, U1.49 (PD4/FD12)
/LED_CY: R13.1, U1.47 (PD2/FD10)
/LED_ERR: R16.1, U1.50 (PD5/FD13)
/LED_FPGA: R14.1, U1.48 (PD3/FD11)
/OE: U1.35 (PA2/SLOE), U30.L3 (IOB_71)
/PKTEND: U1.39 (PA6/PKTEND), U30.L1 (IOB_56)
/RD: U1.1 (RDY0/SLRD), U30.J5 (IOB_78)
/SCL: R2.1, TP5.1 (1_1), TP11.1 (1_1), U1.15 (SCL), U2.6 (SCL), U3.6 (SCL), U30.H9 (IOB_104_CBSEL1)
/SDA: R1.1, TP4.1 (1_1), TP10.1 (1_1), U1.16 (SDA), U2.5 (SDA), U3.5 (SDA), U30.J8 (IOB_91)
/SHLD: C13.1, R3.1
/USB_N: TP16.1 (1_1), U1.9 (D-)
/USB_P: TP15.1 (1_1), U1.8 (D+)
/VCCPLL0: C76.1, C78.1, R31.1, U30.J6 (VCCPLL0)
/VCCPLL1: C79.1, C80.1, R32.1, U30.C6 (VCCPLL1)
/VUSB: C8.1, FB1.2
/WR: U1.2 (RDY1/SLWR), U30.J4 (IOB_64)
/XTALIN: C12.1, U1.5 (XTALIN)
/XTALOUT: C11.1, U1.4 (XTALOUT)
/xVBUS: FB1.1, TP13.1 (1_1)
/~ALERT: R17.1, U1.33 (PA0/~INT0), U30.K4 (IOB_73)
/~CY_RESET: C88.1, R5.2, U1.42 (~RESET)
/~FPGA_RESET: R9.2, U1.34 (PA1/~INT1), U30.L9 (~CRESET)
GND: C1.2, C2.2, C3.2, C4.2, C5.2, C6.2, C7.2, C8.2, C9.2, C10.2, C11.2, C12.2, C13.2, C14.2, C15.2, C16.2, C17.2, C18.2, C19.2, C20.2, C21.2, C23.2, C24.2, C25.2, C26.1, C27.2, C28.2, C77.2, C81.2, C86.1, C87.2, C88.2, C89.2, D1.1 (K), D2.1 (K), D3.1 (K), D4.1 (K), D5.1 (K), R3.2, R9.1, R18.2, R19.2, R52.1, R53.1, TP12.1 (1_1), TP14.1 (1_1), U1.6 (AGND), U1.10 (AGND), U1.12 (GND), U1.14 (RESERVED), U1.26 (GND), U1.28 (GND), U1.41 (GND), U1.53 (GND), U1.56 (GND), U1.57 (EP), U2.4 (GND), U3.4 (GND), U30.E5 (GND), U30.E6 (GND), U30.E7 (GND), U30.F5 (GND), U30.F6 (GND), U30.F7 (GND), U30.G5 (GND), U30.G6 (GND), U30.G7 (GND), U30.H5 (GND)
unnamed: D1.2 (A), R12.2
unnamed: D2.2 (A), R13.2
unnamed: D3.2 (A), R14.2
unnamed: D4.2 (A), R15.2
unnamed: D5.2 (A), R16.2
unnamed: R4.2, R5.1

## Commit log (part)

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2026-05-04 Add initial project plan for KiCad Smart Auto-Placer
2026-05-04 feat: add PCB data model and KiCad parser
    - BoardModel, Component, Net, Pad, BoardOutline with JSON serialization
    - S-expression parser for .kicad_pcb with net ID→name resolution
    - Board outline extraction from Edge.Cuts
    - Component type inference from reference/footprint
2026-05-04 feat: add optimization engine (clustering, cost, grid placement)
    - Net hypergraph with greedy and Louvain clustering
    - HPWL cost function (clique model ≤4 pins, star model >4 pins)
    - Overlap and boundary penalty functions
    - Grid placement with edge-aware connector positioning
2026-05-04 feat: add legalization and placement application
    - Grid snapping, boundary enforcement, iterative overlap resolution
    - Placement writer to apply positions back to .kicad_pcb
    - Position JSON export for verification
2026-05-04 feat: add board profiles and CLI interface
    - 5 built-in profiles: mcu_peripheral, power_supply, rf_frontend, mixed_signal, generic
    - Per-rule constraint weights with YAML save/load
    - CLI: extract, place, cost, profiles commands
    - Interactive profile tuning mode"
2026-05-04 test: add sample MCU board and Phase 1 test suite
    - Sample 18-component MCU peripheral board
    - 27 tests covering: data model, parser, clustering, HPWL, grid placement, legalization, profiles, and end-to-end pipeline
2026-05-04 feat: add initial README structure with project directory layout
2026-05-04 add .gitignore to exclude KiCad PCB files and Python cache directories
2026-05-04 feat: add greedy-swap optimizer
    - add CLI --optimize flag
    - fix test helper name
2026-05-05 fix: update coordinate mapping to use millimeters and improve formatting
2026-05-05 fix: update .gitignore to exclude backup and JSON files
2026-05-05 fix: update .gitignore to exclude milestone and plan files
2026-05-05 feat: add claude.md for KiCad Smart Auto-Placer
2026-05-05 fix: update default legalization grid value to 1.8 mm
2026-05-06 fix: update .gitignore to include config.json
2026-05-06 feat: add initial config.json for placement and legalization settings
2026-05-07 feat: add pad rotation handling to maintain copper layer orientation
2026-05-07 chore: remove auto_placer_plan.md as part of project restructuring
2026-05-08 feat: add logo
2026-05-08 fix: update logo size in README and add logo file reference
2026-05-08 feat: enhance smart placement with vertical connector detection and simulated annealing optimization
2026-05-09 fix: connector overlap and components (R,C) pushed onto connectors implement rotation-aware connector spacing interior bbox expansion for edge connectors
2026-05-09 feat: enhance overlap resolution by adjusting push behavior for edge connectors
2026-05-09 fix: change default placement algorithm from force-directed to grid
2026-05-09 fix: connector overlap at edges when pcb outline is not define also fix clustering: after optimisation components tends to cluster in a corner pull them back to the center
2026-05-09 feat: add pad_bbox function for natuarlly over hanging connectors
2026-05-09 feat: wire constraint rules through the entire pipeline.
2026-05-09 fix: resolve SA accept=0 freeze and improve placement quality
    Root cause: annealer.py computed old_cost without the constraint penalty
    term, while new_cost (via cost_state.incremental_update) included it.
    This made delta always huge positive → exp(-delta/T) ≈ 0 → accept=0.
    Key fixes:
    - Add CONSTRAINT_WEIGHT * constraint_total * scale to old_cost formula
    - Replace quadratic penalties (excess**2) with linear (excess) across
2026-05-10 feat(SA): v8 strategy — faster runtime, overlap resolver, power-rail clustering
    Reworks the simulated annealing strategy for faster convergence and guaranteed overlap resolution. But still need more optimization:
    SA engine (engine/annealer.py):
    - Moderate penalty discount (penalty_scale_min=0.65): hot SA has effective overlap weight = 6.5, enough to limit overlaps while exploring; cold SA ramps to full weight for resolution
    - Faster runtime: 200 main iterations (was 300), 2 reheats (was 3), 0.97 near-freeze cooling (was 0.995), earlier freeze detection (T < 5% T0 instead of 1% T0)
    - T0 calibration: set penalty_scale before sampling, use 75th percentile of positive deltas for higher
2026-05-10 fix: add .history/ to .gitignore to prevent tracking of history files
2026-05-10 fix: exclude edge connectors from out-of-bounds counts in cost functions
    Edge connectors that overhang the board edge are still counted as out-of-bounds by count_out_of_bounds() and BoardModel.stats(). These connectors are intentionally placed with pads inside the board a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
2026-05-10 fix: exclude edge connectors from out-of-bounds checks
    Edge connectors that overhang the board edge are still counted as out-of-bounds by count_out_of_bounds() and BoardModel.stats().
    These connectors are intentionally placed with pads inside the board and bodies overhanging.
    So exclude them from OOB calculation.
2026-05-10 feat: update project readme
2026-05-10 refactor: remove unused parameters and functions
2026-05-10 feat: update annealing parameters and optimization strategies for improved performance
2026-05-10 fix (try 1): Enhance overlap resolution and boundary enforcement
    - Updated simulated annealing (SA) strategy to use density-adaptive parameters for better performance on dense and sparse boards.
    - Replaced SA's overlap resolver with a smarter greedy resolver that prevents new overlaps during resolution.
    - Improved grid snapping to be overlap-aware, checking for overlaps after snapping and adjusting positions accordingly.
    - Enhanced boundary enforcement to avoid creating new overlaps when clamping components, with a fallback to sliding along the boundary.
    - Introduced a greedy resolution strategy that nudges overlapping components to free positions, including a grid sweep for dense boards.
2026-05-10 tests: add test pcbs
2026-05-11 feat(placement): improve SA tracking, board sizing, revert logic, and legalizer scoring
    This change combines the SA stability fixes, density-aware board expansion,
    and legalizer scoring updates into one placement pipeline improvement.
    Highlights:
    - Fix SA drift by resyncing cost state periodically and saving verified best states
    - Preserve the global best across reheats and avoid false reverts from mixed penalty scales
    - Allow limited exploration from zero-overlap starts so SA does not freeze
2026-05-11 feat(tests): add script to run placement pipeline with logging and summary output
2026-05-11 fix: update SA parameters and switch default profile to generic
2026-05-11 fix: add *placed.kicad_pcb to .gitignore
2026-05-11 feat(Placemnet): disable global SA and just use greedy swap
    Enhanced _greedy_refine() - Added enhanced mode with:
    - Finer nudge distances (11 steps from 0.01 to 6.0mm vs 6 steps)
    - Lower improve threshold (0.1 vs 0.5) - more aggressive acceptance
    - Adaptive sweep count based on component count
    - HPWL-contribution ordering (high-HPWL components processed first)
    - HPWL printed in greedy sweep logs
2026-05-11 feat(Placement): add smart swap Added _build_swap_candidates() — Smart candidate filtering with 3 strategies: - Net-connected: Components sharing signal nets (highest value swaps) - Size-class: Compo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
    Added _try_single_swap() - Extracted swap logic into clean helper function
    Modified _greedy_swap_refine() - Uses candidate map instead of brute-force all-pairs
2026-05-12 fix(Legalization): Distributes caps evenly across ICs sharing a power rail
2026-06-24 fix(Legalization): Abacus respects decoupling topology + per-edge connectors
2026-06-28 feat(Density): implement density penalty for component clustering and pre-place decoupling caps
2026-06-30 perf: pure-Python Louvain, lazy YAML, deterministic SA, cached is_edge_connector
    - net_clustering: new engine/_pure_graph.py replaces networkx (Graph + Louvain)
    - board_profiles: PyYAML loaded lazily — default pipeline no longer requires it
    - cost_function: merge overlap area + count into single O(n²) pass
    - annealer: sorted _comp_nets for deterministic swap-candidate order
    - constraint_evaluator: sorted power_nets/net_caps iteration — deterministic
    cap→IC assignment (set iteration order varies with id() under ASLR)
